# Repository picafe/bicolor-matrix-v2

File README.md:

# Bicolour Matrix

A 32x8 bicolor LED matrix module composed of 4 8x8 matrices based on the Holtek HT16K33A I2C LED driver. V1 paired it with a stacked adapter (RP2040 Zero + DS3231 module); V2 redesigns the matrix routing and puts an ESP32-C3, RTC, and environment sensors on a half-length adapter board behind the display.

*V1 running as a clock*

## Inspiration

Inspired by the common 32x8 red LED matrix modules that use the MAX7219 IC, I wanted to make my own module but with more colours and functionality, while keeping the same asthetic.

I found [these](https://www.aliexpress.com/item/1005007029570407.html) modules while browsing Aliexpress and thought they could look be a cool alternative, costing ~$15 for 10 modules. With the red and light green variant, you can have red, a light green, and orange all in one module. As far as I'm aware, there aren't RGB modules in a similar form factor, although you can take generic WS2818 8x8 matricies and 3D print a diffuser for them, although the footprint is much bigger. This project was also partially inspired by [bitluni's LED magnet tiles](https://www.youtube.com/watch?v=L2J_eNgjxio) which I found really cool.

Unlike the single colour matricies with 16 pins, these had 24. I found [this](https://www.adafruit.com/product/902) Adafruit module and followed a similar schematic with the Holtek HT16K33A I2C LED driver.

For V2 I revisited the HT16K33A datasheet and realized any ROW/COL pin can map to any matrix row/column, thus routing got a lot simpler than matching Adafruit's pinout exactly.

## Structure

| Board | Role |
| --- | --- |
| **bicolour-matrix** | 32×8 display: 4× HT16K33A + 4× 8×8 bicolour matrices |
| **adapter-board-r2** | ESP32-C3-WROOM-02, CH340X USB-UART, YSN8900 RTC + CR2032, STCC4 (default CO₂; optional SCD41), SHT4x, BMP580, LIS2DW12 |
| **button-board-r2** *(optional / WIP)* | OLED + light sensor + touch pads |

The adapter is half the length of the matrix board and mates with a pin header between the middle modules so that the stack stays stable without a case.

The button board is a separate interface that is connected to the adapter board with a 7-pin JST SH connector. This is meant to be customized and built by the user themselves, although I've included a sample design with an OLED, light sensor, and 2x touch pads you can start from. What you include and how you integrate it is up to you and how you want to design an enclosure.

## Pictures

### Assembled (V1)

### V2 

#### 3D

*Adapter board R2 (3D)*

*Matrix board R2 (3D)*

#### Schematics

*Matrix board schematic*

*Adapter board R2 schematic*

#### PCB

*Matrix board PCB (four HT16K33A modules)*

*Adapter board R2 PCB*

## Bill of materials

Prices are estimated from LCSC single-board quantities and AliExpress for the LED matrices.

### Matrix board (`bicolour-matrix`)

| Designator | Value | Footprint | Qty | LCSC | Unit cost (est.) | Line total (est.) |
| --- | --- | --- | --- | --- | --- | --- |
| C1, C6 | 10 µF | 0805 | 2 | C440198 | $0.02 | $0.04 |
| C2, C3, C4, C5 | 100 nF | 0603 | 4 | C14663 | $0.01 | $0.04 |
| D1, D2, D3, D4 | 1N4148WS | SOD-323 | 4 | C2128 | $0.01 | $0.04 |
| J1, J2 | 1×04 pin header | Through hole | 2 | — | $0.05 | $0.10 |
| J3, J4 | JST SH 1×04 (Qwiic-style) | SMD | 2 | — | $0.15 | $0.30 |
| J5 | 1×02 socket | Through hole | 1 | — | $0.05 | $0.05 |
| LED1, LED2, LED3, LED4 | 8×8 bicolour matrix | Module | 4 | AliExpress | $2.00 | $8.00 |
| R3, R4, R5, R9, R10, R11, R13, R14, R15, R18, R19, R20 | 47 kΩ | 0603 | 12 | C25819 | $0.002 | $0.02 |
| U1, U2, U3, U4 | HT16K33A | SSOP-28 | 4 | C5444738 | $0.54 | $2.16 |
| | | | | **Total (matrix, components only)** | | **~$10.75** |

### Adapter board (`adapter-board-r2`)

Default build uses the STCC4 for CO₂. An SCD41 (U7) can be fitted instead if R6/R8 are left open and the unpopulated R5/R7 0 Ω jumpers are fitted (routes the SHT4x onto the main I²C bus instead of the STCC4 compensation bus).

| Designator | Value | Footprint | Qty | LCSC | Unit cost (est.) | Line total (est.) |
| --- | --- | --- | --- | --- | --- | --- |
| BT1 | CR2032 holder | SMD | 1 | C7498149 | $0.15 | $0.15 |
| C1 | 1 µF | 0603 | 1 | C15849 | $0.01 | $0.01 |
| C3, C5, C11, C12, C18 | 100 nF | 0603 | 5 | C14663 | $0.01 | $0.05 |
| C4, C8, C9, C10, C13, C14, C16, C17 | 100 nF | 0402 | 8 | C1525 | $0.005 | $0.04 |
| C15 | 10 µF | 0603 | 1 | C19702 | $0.02 | $0.02 |
| C2 | 10 µF | 0805 | 1 | C15850 | $0.03 | $0.03 |
| C6, C7 | 4.7 µF | 1206 | 2 | C29823 | $0.03 | $0.06 |
| D1 | B5817WS | SOD-323 | 1 | C7420329 | $0.05 | $0.05 |
| F1, F2 | 1.1 A fuse | 0805 | 2 | — | $0.05 | $0.10 |
| J1 | USB-C receptacle 14P | Through hole | 1 | C3151746 | $0.30 | $0.30 |
| J2 | JST SH 1×07 | SMD | 1 | — | $0.25 | $0.25 |
| J3 | 1×02 socket | Through hole | 1 | — | $0.05 | $0.05 |
| J4 | 1×04 socket | Through hole | 1 | — | $0.08 | $0.08 |
| Q1 | UMH3N | SOT-363 | 1 | — | $0.08 | $0.08 |
| Q2, Q3 | BSS138W | SOT-323 | 2 | C28646265 | $0.03 | $0.06 |
| R1, R2 | 10 kΩ | 0603 | 2 | C25804 | $0.002 | $0.004 |
| R3, R4 | 5.1 kΩ | 0603 | 2 | C23186 | $0.002 | $0.004 |
| R6, R8 | 0 Ω (STCC4 / SHT4x compensation) | 0402 | 2 | C17168 | $0.004 | $0.008 |
| R9, R10, R11, R12 | 4.7 kΩ | 0603 | 4 | C23162 | $0.002 | $0.008 |
| S1, S2 | Tactile button, 160 gf | PTS810 | 2 | C720477 | $0.10 | $0.20 |
| U1 | ESP32-C3-WROOM-02 | Module | 1 | C2934560 | $3.13 | $3.13 |
| U2 | USBLC6-2SC6 | SOT-23-6 | 1 | C7519 | $0.18 | $0.18 |
| U3 | CH340X | MSOP-10 | 1 | C3035748 | $0.67 | $0.67 |
| U4 | AP2114HA-3.3TRG1 | SOT-223 | 1 | C460314 | $0.25 | $0.25 |
| U5 | YSN8900AP3 | SMD3225-10P | 1 | C54780223 | $1.46 | $1.46 |
| U6 | SHT4x | DFN-4 | 1 | — | $1.20 | $1.20 |
| U8 | BMP580 | LGA-10 | 1 | C22391138 | $0.96 | $0.96 |
| U9 | LIS2DW12TR | LGA-12 | 1 | C189624 | $1.26 | $1.26 |
| U10 | STCC4 | LGA | 1 | C49191471 | $10.06 | $10.06 |
| | | | | **Total (adapter, default build)** | | **~$20.73** |

Optional (not in default total): U7 SCD41 (~$18, C3659421) with R5/R7 fitted and R6/R8 open; leave U10 unpopulated.

**Combined components (matrix + adapter, default): ~$31.48**  
*(PCBs: ~$30 matrix + ~$12 adapter at JLCPCB)*

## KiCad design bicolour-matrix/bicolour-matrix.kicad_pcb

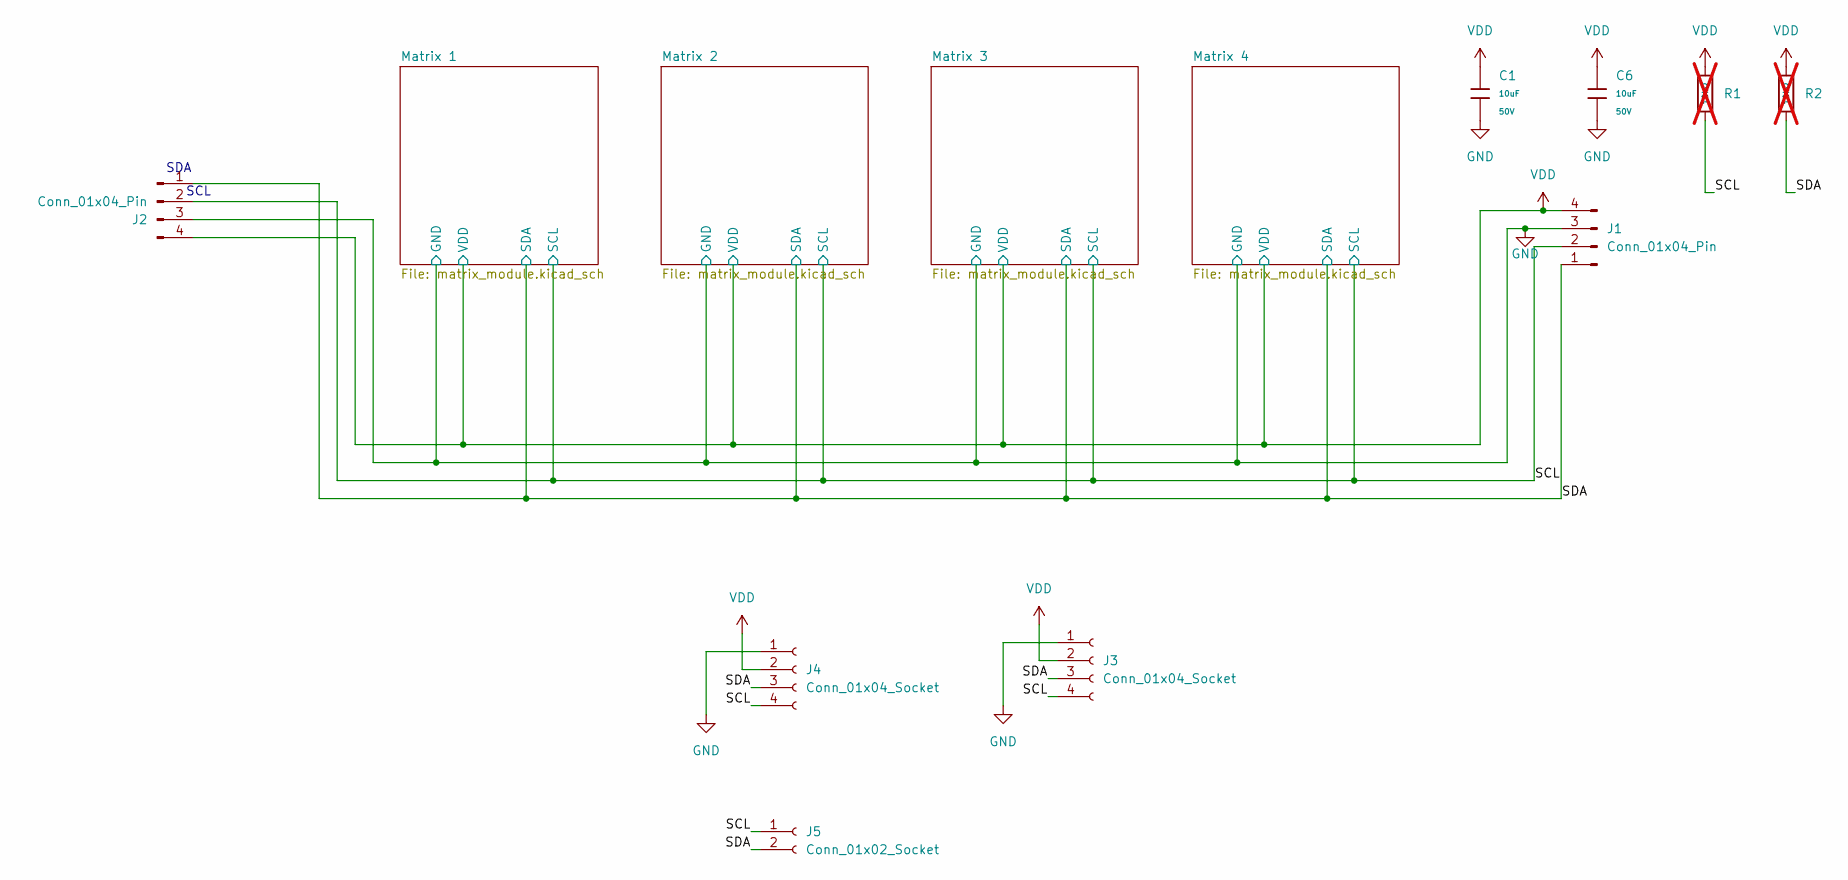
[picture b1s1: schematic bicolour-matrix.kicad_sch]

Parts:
C1, C6: 10uF; C_0805; Voltage Rated 50V; Tolerance ±10%; Part GRM21BR61H106KE43L; LCSC C440198
J1, J2: Conn_01x04_Pin; PinHeader_1x04_P2.54mm_Vertical
J3, J4: Conn_01x04_Socket; JST_SH_SM04B-SRSS-TB_1x04-1MP_P1.00mm_Horizontal
J5: Conn_01x02_Socket; PinSocket_1x02_P2.54mm_Vertical
R1, R2: 10kΩ; R_0603_1608Metric; Overload Voltage (Max) 75V; Tolerance ±1%; Part 0603WAF1002T5E; LCSC C25804; not fitted

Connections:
/SCL: J1.2, J2.2, J3.4, J4.4, J5.1, R1.2; also elsewhere on the board
/SDA: J1.1, J2.1, J3.3, J4.3, J5.2, R2.2; also elsewhere on the board
GND: C1.2, C6.2, J1.3, J2.3, J3.1, J4.1; also elsewhere on the board
VDD: C1.1, C6.1, J1.4, J2.4, J3.2, J4.2, R1.1, R2.1; also elsewhere on the board

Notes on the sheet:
SDA
SCL

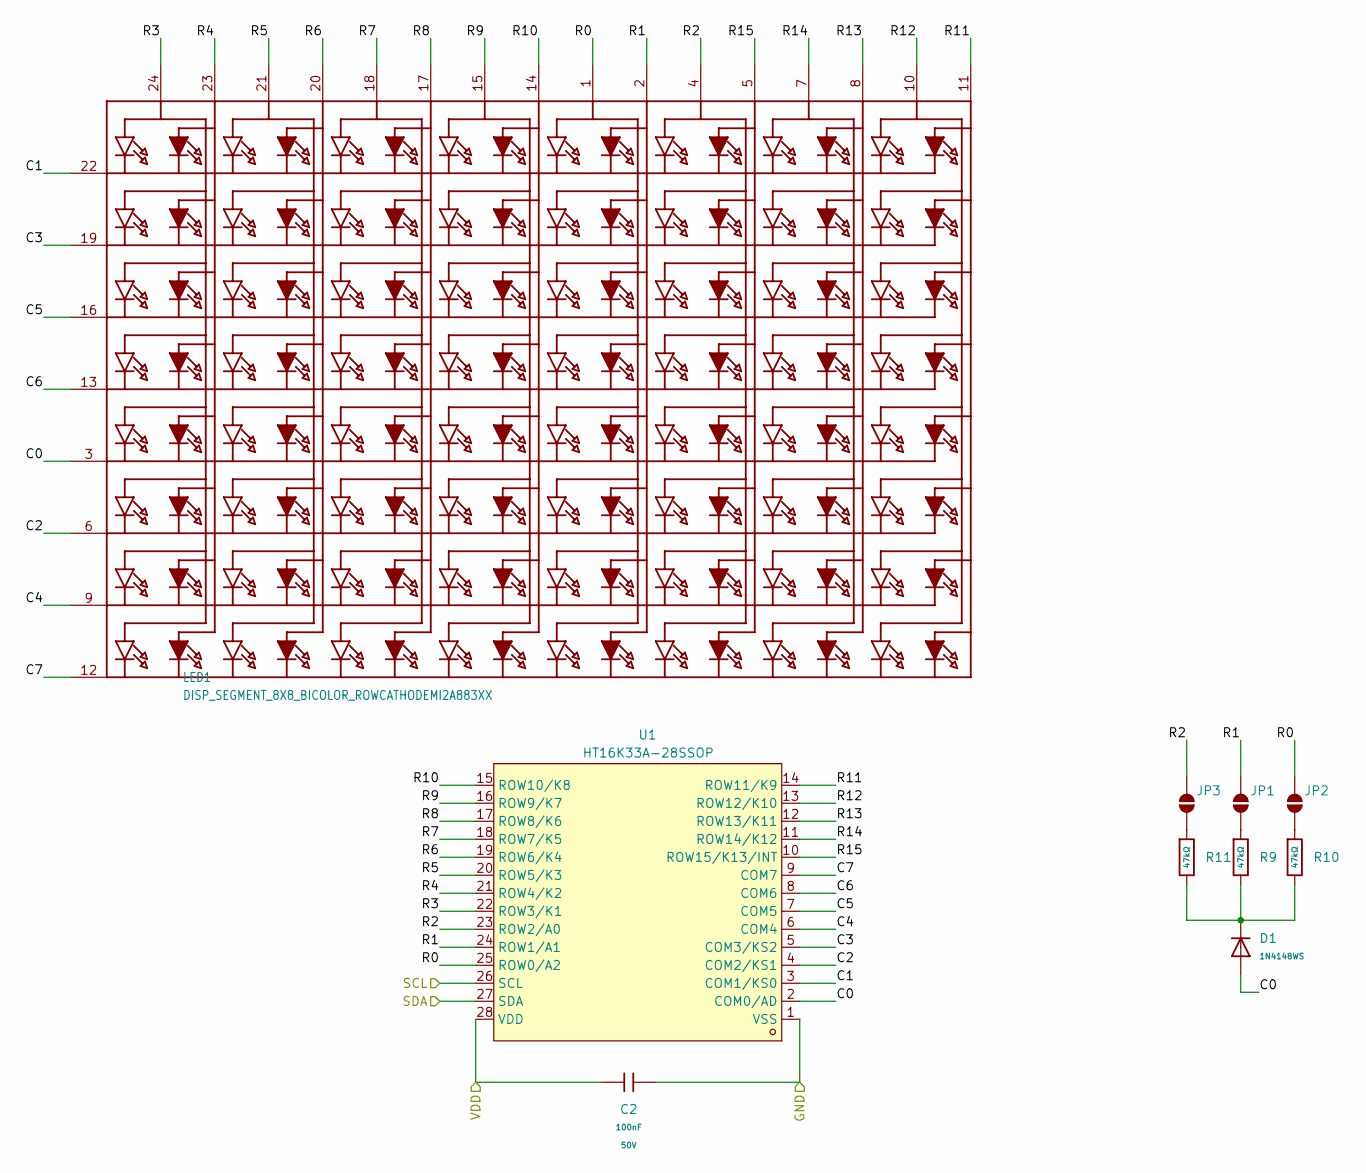
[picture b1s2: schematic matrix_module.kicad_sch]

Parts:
C2: 100nF; C_0603; Voltage Rated 50V; Tolerance ±10%; Part CC0603KRX7R9BB104; LCSC C14663
D1: 1N4148WS; D_SOD-323; Forward Voltage (Vf@If) 1.25V@150mA; Reverse Voltage (Vr) 100V; Part 1N4148WS; LCSC C2128
JP1, JP2, JP3: SolderJumper_2_Open; SolderJumper-2_P1.3mm_Open_RoundedPad1.0x1.5mm
LED1: DISP_SEGMENT_8X8_BICOLOR_ROWCATHODEMI2A883XX; SEGMENT_BICOL_BL-M12A883XX
R9, R10, R11: 47kΩ; R_0603; Overload Voltage (Max) 75V; Tolerance ±1%; Part 0603WAF4702T5E; LCSC C25819
U1: HT16K33A-28SSOP; SSOP-28_3.9x9.9mm_P0.635mm; LCSC Part C5444738

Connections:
/Matrix 1/C0: D1.2, LED1.3 (K5), U1.2 (COM0/AD)
/Matrix 1/C1: LED1.22 (K1), U1.3 (COM1/KS0)
/Matrix 1/C2: LED1.6 (K6), U1.4 (COM2/KS1)
/Matrix 1/C3: LED1.19 (K2), U1.5 (COM3/KS2)
/Matrix 1/C4: LED1.9 (K7), U1.6 (COM4)
/Matrix 1/C5: LED1.16 (K3), U1.7 (COM5)
/Matrix 1/C6: LED1.13 (K4), U1.8 (COM6)
/Matrix 1/C7: LED1.12 (K8), U1.9 (COM7)
/Matrix 1/R0: JP2.2 (B), LED1.1 (A9), U1.25 (ROW0/A2)
/Matrix 1/R1: JP1.2 (B), LED1.2 (A10), U1.24 (ROW1/A1)
/Matrix 1/R2: JP3.2 (B), LED1.4 (A11), U1.23 (ROW2/A0)
/Matrix 1/R3: LED1.24 (A1), U1.22 (ROW3/K1)
/Matrix 1/R4: LED1.23 (A2), U1.21 (ROW4/K2)
/Matrix 1/R5: LED1.21 (A3), U1.20 (ROW5/K3)
/Matrix 1/R6: LED1.20 (A4), U1.19 (ROW6/K4)
/Matrix 1/R7: LED1.18 (A5), U1.18 (ROW7/K5)
/Matrix 1/R8: LED1.17 (A6), U1.17 (ROW8/K6)
/Matrix 1/R9: LED1.15 (A7), U1.16 (ROW9/K7)
/Matrix 1/R10: LED1.14 (A8), U1.15 (ROW10/K8)
/Matrix 1/R11: LED1.11 (A16), U1.14 (ROW11/K9)
/Matrix 1/R12: LED1.10 (A15), U1.13 (ROW12/K10)
/Matrix 1/R13: LED1.8 (A14), U1.12 (ROW13/K11)
/Matrix 1/R14: LED1.7 (A13), U1.11 (ROW14/K12)
/Matrix 1/R15: LED1.5 (A12), U1.10 (ROW15/K13/INT)
/SCL: U1.26 (SCL); also elsewhere on the board
/SDA: U1.27 (SDA); also elsewhere on the board
GND: C2.2, U1.1 (VSS); also elsewhere on the board
unnamed: D1.1, R9.2, R10.2, R11.2
unnamed: JP1.1 (A), R9.1
unnamed: JP2.1 (A), R10.1
unnamed: JP3.1 (A), R11.1
VDD: C2.1, U1.28 (VDD); also elsewhere on the board

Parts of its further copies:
C3, C4, C5: 100nF; C_0603; Voltage Rated 50V; Tolerance ±10%; Part CC0603KRX7R9BB104; LCSC C14663
D2, D3, D4: 1N4148WS; D_SOD-323; Forward Voltage (Vf@If) 1.25V@150mA; Reverse Voltage (Vr) 100V; Part 1N4148WS; LCSC C2128
JP4, JP5, JP6, JP7, JP8, JP9, JP10, JP11, JP12: SolderJumper_2_Open; SolderJumper-2_P1.3mm_Open_RoundedPad1.0x1.5mm
LED2, LED3, LED4: DISP_SEGMENT_8X8_BICOLOR_ROWCATHODEMI2A883XX; SEGMENT_BICOL_BL-M12A883XX
R3, R4, R5, R13, R14, R15, R18, R19, R20: 47kΩ; R_0603; Overload Voltage (Max) 75V; Tolerance ±1%; Part 0603WAF4702T5E; LCSC C25819
U2, U3, U4: HT16K33A-28SSOP; SSOP-28_3.9x9.9mm_P0.635mm; LCSC Part C5444738

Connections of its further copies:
/Matrix 2/C0: D2.2, LED2.3 (K5), U2.2 (COM0/AD)
/Matrix 2/C1: LED2.22 (K1), U2.3 (COM1/KS0)
/Matrix 2/C2: LED2.6 (K6), U2.4 (COM2/KS1)
/Matrix 2/C3: LED2.19 (K2), U2.5 (COM3/KS2)
/Matrix 2/C4: LED2.9 (K7), U2.6 (COM4)
/Matrix 2/C5: LED2.16 (K3), U2.7 (COM5)
/Matrix 2/C6: LED2.13 (K4), U2.8 (COM6)
/Matrix 2/C7: LED2.12 (K8), U2.9 (COM7)
/Matrix 2/R0: JP6.2 (B), LED2.1 (A9), U2.25 (ROW0/A2)
/Matrix 2/R1: JP5.2 (B), LED2.2 (A10), U2.24 (ROW1/A1)
/Matrix 2/R2: JP4.2 (B), LED2.4 (A11), U2.23 (ROW2/A0)
/Matrix 2/R3: LED2.24 (A1), U2.22 (ROW3/K1)
/Matrix 2/R4: LED2.23 (A2), U2.21 (ROW4/K2)
/Matrix 2/R5: LED2.21 (A3), U2.20 (ROW5/K3)
/Matrix 2/R6: LED2.20 (A4), U2.19 (ROW6/K4)
/Matrix 2/R7: LED2.18 (A5), U2.18 (ROW7/K5)
/Matrix 2/R8: LED2.17 (A6), U2.17 (ROW8/K6)
/Matrix 2/R9: LED2.15 (A7), U2.16 (ROW9/K7)
/Matrix 2/R10: LED2.14 (A8), U2.15 (ROW10/K8)
/Matrix 2/R11: LED2.11 (A16), U2.14 (ROW11/K9)
/Matrix 2/R12: LED2.10 (A15), U2.13 (ROW12/K10)
/Matrix 2/R13: LED2.8 (A14), U2.12 (ROW13/K11)
/Matrix 2/R14: LED2.7 (A13), U2.11 (ROW14/K12)
/Matrix 2/R15: LED2.5 (A12), U2.10 (ROW15/K13/INT)
/Matrix 3/C0: D3.2, LED3.3 (K5), U3.2 (COM0/AD)
/Matrix 3/C1: LED3.22 (K1), U3.3 (COM1/KS0)
/Matrix 3/C2: LED3.6 (K6), U3.4 (COM2/KS1)
/Matrix 3/C3: LED3.19 (K2), U3.5 (COM3/KS2)
/Matrix 3/C4: LED3.9 (K7), U3.6 (COM4)
/Matrix 3/C5: LED3.16 (K3), U3.7 (COM5)
/Matrix 3/C6: LED3.13 (K4), U3.8 (COM6)
/Matrix 3/C7: LED3.12 (K8), U3.9 (COM7)
/Matrix 3/R0: JP9.2 (B), LED3.1 (A9), U3.25 (ROW0/A2)
/Matrix 3/R1: JP8.2 (B), LED3.2 (A10), U3.24 (ROW1/A1)
/Matrix 3/R2: JP7.2 (B), LED3.4 (A11), U3.23 (ROW2/A0)
/Matrix 3/R3: LED3.24 (A1), U3.22 (ROW3/K1)
/Matrix 3/R4: LED3.23 (A2), U3.21 (ROW4/K2)
/Matrix 3/R5: LED3.21 (A3), U3.20 (ROW5/K3)
/Matrix 3/R6: LED3.20 (A4), U3.19 (ROW6/K4)
/Matrix 3/R7: LED3.18 (A5), U3.18 (ROW7/K5)
/Matrix 3/R8: LED3.17 (A6), U3.17 (ROW8/K6)
/Matrix 3/R9: LED3.15 (A7), U3.16 (ROW9/K7)
/Matrix 3/R10: LED3.14 (A8), U3.15 (ROW10/K8)
/Matrix 3/R11: LED3.11 (A16), U3.14 (ROW11/K9)
/Matrix 3/R12: LED3.10 (A15), U3.13 (ROW12/K10)
/Matrix 3/R13: LED3.8 (A14), U3.12 (ROW13/K11)
/Matrix 3/R14: LED3.7 (A13), U3.11 (ROW14/K12)
/Matrix 3/R15: LED3.5 (A12), U3.10 (ROW15/K13/INT)
/Matrix 4/C0: D4.2, LED4.3 (K5), U4.2 (COM0/AD)
/Matrix 4/C1: LED4.22 (K1), U4.3 (COM1/KS0)
/Matrix 4/C2: LED4.6 (K6), U4.4 (COM2/KS1)
/Matrix 4/C3: LED4.19 (K2), U4.5 (COM3/KS2)
/Matrix 4/C4: LED4.9 (K7), U4.6 (COM4)
/Matrix 4/C5: LED4.16 (K3), U4.7 (COM5)
/Matrix 4/C6: LED4.13 (K4), U4.8 (COM6)
/Matrix 4/C7: LED4.12 (K8), U4.9 (COM7)
/Matrix 4/R0: JP12.2 (B), LED4.1 (A9), U4.25 (ROW0/A2)
/Matrix 4/R1: JP11.2 (B), LED4.2 (A10), U4.24 (ROW1/A1)
/Matrix 4/R2: JP10.2 (B), LED4.4 (A11), U4.23 (ROW2/A0)
/Matrix 4/R3: LED4.24 (A1), U4.22 (ROW3/K1)
/Matrix 4/R4: LED4.23 (A2), U4.21 (ROW4/K2)
/Matrix 4/R5: LED4.21 (A3), U4.20 (ROW5/K3)
/Matrix 4/R6: LED4.20 (A4), U4.19 (ROW6/K4)
/Matrix 4/R7: LED4.18 (A5), U4.18 (ROW7/K5)
/Matrix 4/R8: LED4.17 (A6), U4.17 (ROW8/K6)
/Matrix 4/R9: LED4.15 (A7), U4.16 (ROW9/K7)
/Matrix 4/R10: LED4.14 (A8), U4.15 (ROW10/K8)
/Matrix 4/R11: LED4.11 (A16), U4.14 (ROW11/K9)
/Matrix 4/R12: LED4.10 (A15), U4.13 (ROW12/K10)
/Matrix 4/R13: LED4.8 (A14), U4.12 (ROW13/K11)
/Matrix 4/R14: LED4.7 (A13), U4.11 (ROW14/K12)
/Matrix 4/R15: LED4.5 (A12), U4.10 (ROW15/K13/INT)
/SCL: U2.26 (SCL), U3.26 (SCL), U4.26 (SCL); also elsewhere on the board
/SDA: U2.27 (SDA), U3.27 (SDA), U4.27 (SDA); also elsewhere on the board
GND: C3.2, C4.2, C5.2, U2.1 (VSS), U3.1 (VSS), U4.1 (VSS); also elsewhere on the board
unnamed: D2.1, R3.2, R4.2, R5.2
unnamed: D3.1, R13.2, R14.2, R15.2
unnamed: D4.1, R18.2, R19.2, R20.2
unnamed: JP4.1 (A), R3.1
unnamed: JP5.1 (A), R4.1
unnamed: JP6.1 (A), R5.1
unnamed: JP7.1 (A), R13.1
unnamed: JP8.1 (A), R14.1
unnamed: JP9.1 (A), R15.1
unnamed: JP10.1 (A), R18.1
unnamed: JP11.1 (A), R19.1
unnamed: JP12.1 (A), R20.1
VDD: C3.1, C4.1, C5.1, U2.28 (VDD), U3.28 (VDD), U4.28 (VDD); also elsewhere on the board

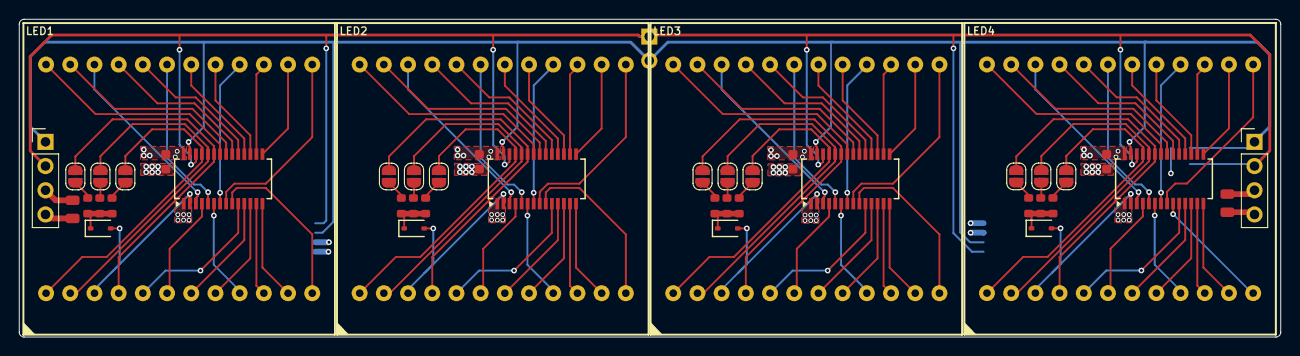
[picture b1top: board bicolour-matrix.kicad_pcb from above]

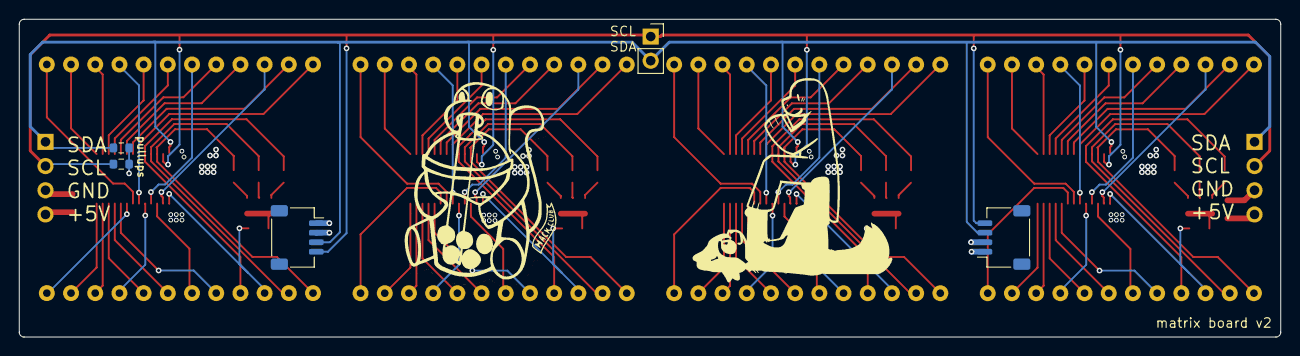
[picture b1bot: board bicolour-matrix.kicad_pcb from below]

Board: 4 copper layers, 132.4 x 33.4 mm, 49 parts (5 on the bottom side), 116 nets.

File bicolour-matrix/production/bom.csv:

Designator,Footprint,Quantity,Value,LCSC Part #
"C1, C6",C_0805,2,10uF,C440198
"C2, C3, C4, C5",C_0603,4,100nF,C14663
"D1, D2, D3, D4",D_SOD-323,4,1N4148WS,C2128
"J1, J2",PinHeader_1x04_P2.54mm_Vertical,2,Conn_01x04_Pin,
"J3, J4",JST_SH_SM04B-SRSS-TB_1x04-1MP_P1.00mm_Horizontal,2,Conn_01x04_Socket,
J5,PinSocket_1x02_P2.54mm_Vertical,1,Conn_01x02_Socket,
"LED1, LED2, LED3, LED4",SEGMENT_BICOL_BL-M12A883XX,4,DISP_SEGMENT_8X8_BICOLOR_ROWCATHODEMI2A883XX,
"R10, R11, R13, R14, R15, R18, R19, R20, R3, R4, R5, R9",R_0603,12,47kΩ,C25819
"U1, U2, U3, U4",SSOP-28_3.9x9.9mm_P0.635mm,4,HT16K33A-28SSOP,C5444738

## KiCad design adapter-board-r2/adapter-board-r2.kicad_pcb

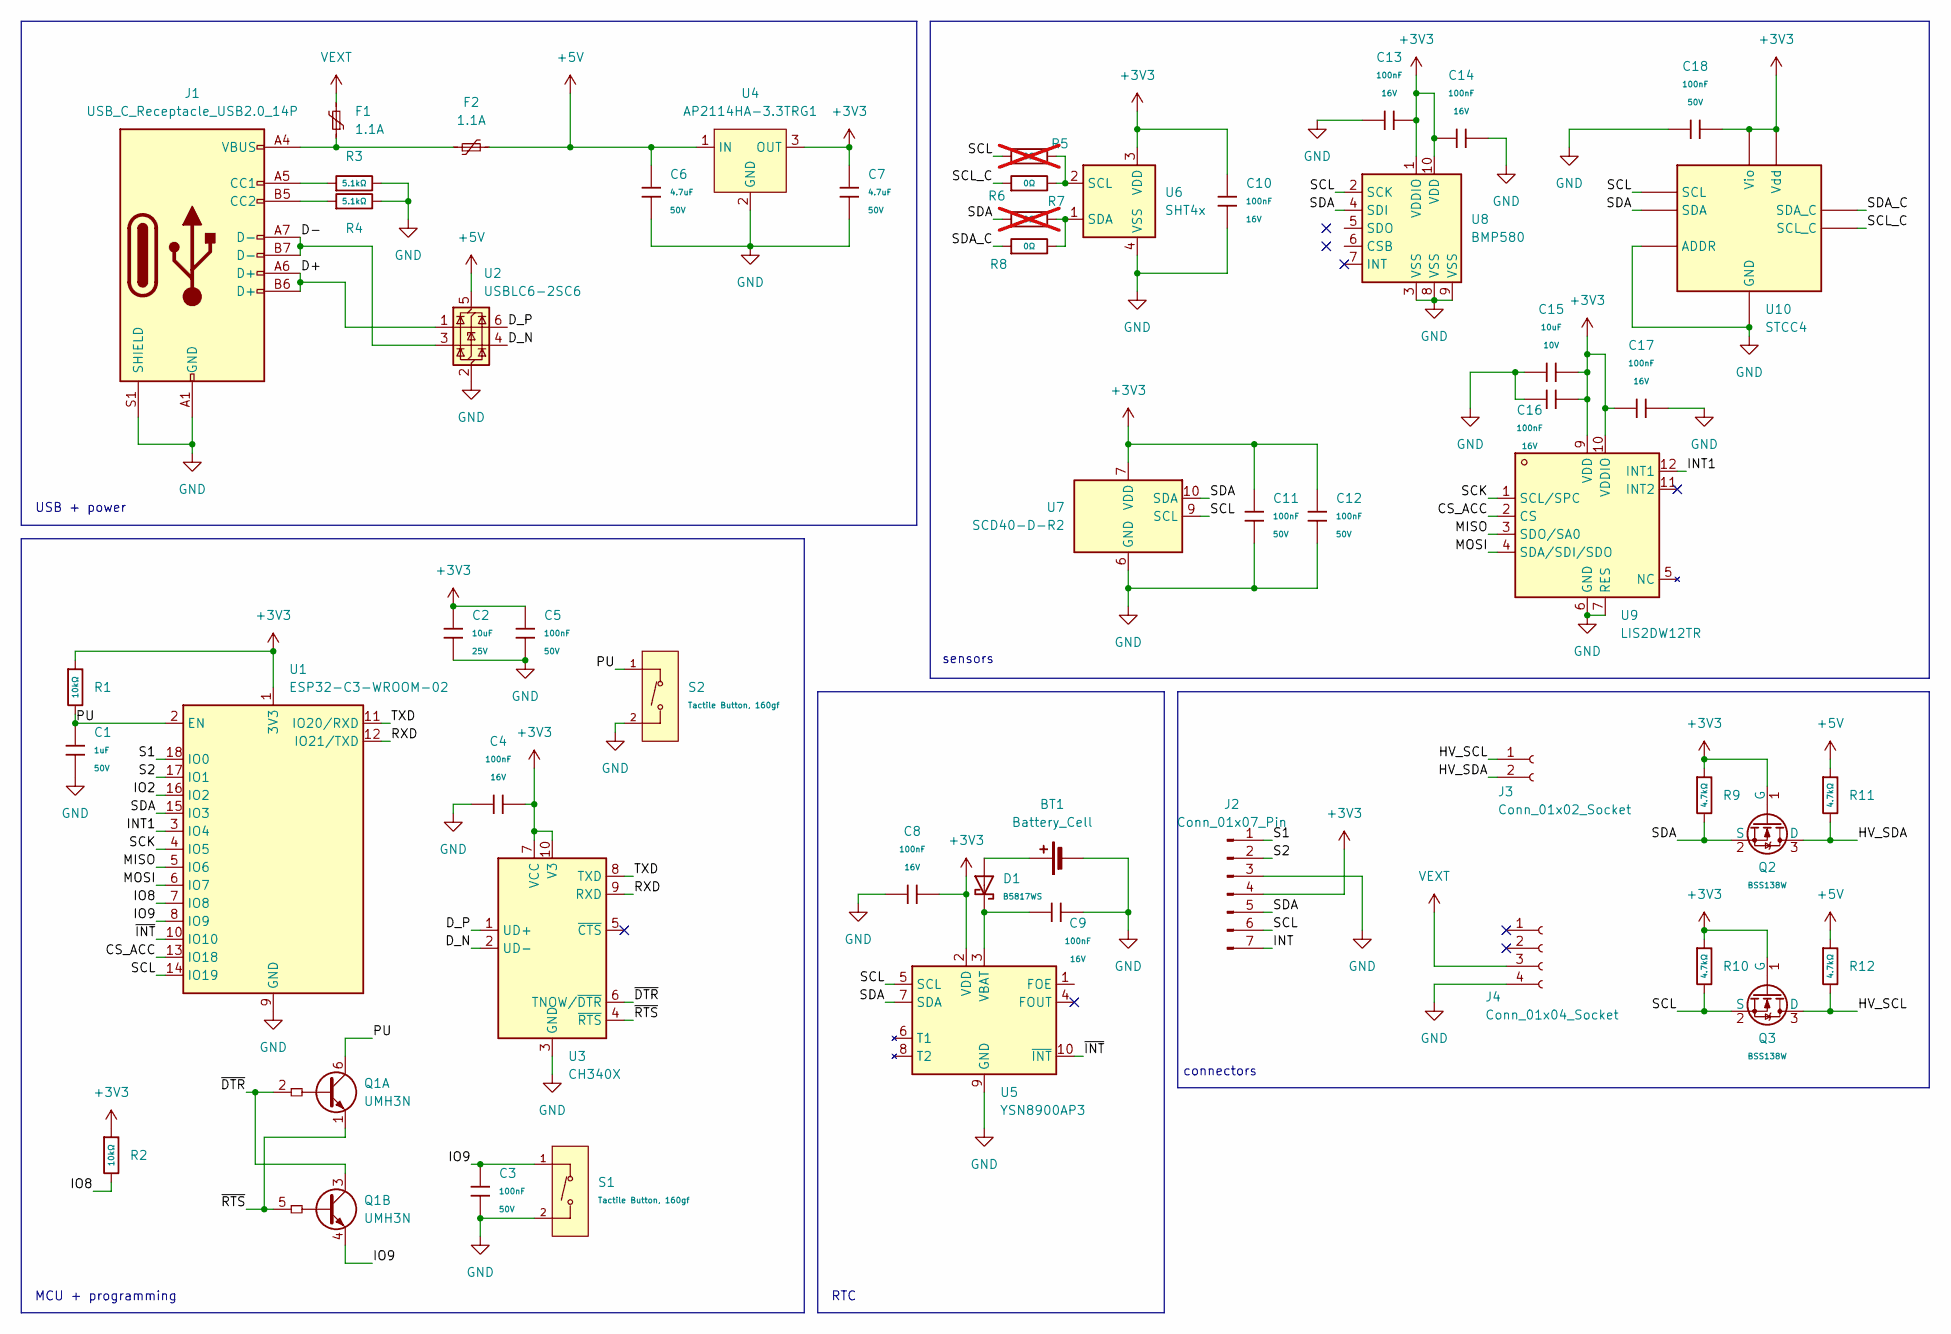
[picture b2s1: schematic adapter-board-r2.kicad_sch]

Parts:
BT1: Battery_Cell; BatteryHolder_Keystone_1060_1x2032
C1: 1uF; C_0603; Voltage Rated 50V; Tolerance ±10%; Part CL10A105KB8NNNC; LCSC C15849
C2: 10uF; C_0805; Voltage Rated 25V; Tolerance ±10%; Part CL21A106KAYNNNE; LCSC C15850
C3, C5, C11, C12, C18: 100nF; C_0603; Voltage Rated 50V; Tolerance ±10%; Part CC0603KRX7R9BB104; LCSC C14663
C4, C8, C9, C10, C13, C14, C16, C17: 100nF; C_0402; Voltage Rated 16V; Tolerance ±10%; Part CL05B104KO5NNNC; LCSC C1525
C6, C7: 4.7uF; C_1206; Voltage Rated 50V; Tolerance ±10%; Part 1206B475K500NT; LCSC C29823
C15: 10uF; C_0603; Voltage Rated 10V; Tolerance ±10%; Part CL10A106KP8NNNC; LCSC C19702
D1: B5817WS; D_SOD-323; Forward Voltage (Vf@If) 450mV@1.0A; Reverse Voltage (Vr) 20V; Part B5817WS; LCSC C7420329
F1, F2: 1.1A; Fuse_0805_2012Metric
J1: USB_C_Receptacle_USB2.0_14P; USB-C-TH_SHOUHAN_TYPE-C-14PLC-H10.0
J2: Conn_01x07_Pin; JST_SH_SM07B-SRSS-TB_1x07-1MP_P1.00mm_Horizontal
J3: Conn_01x02_Socket; PinSocket_1x02_P2.54mm_Vertical
J4: Conn_01x04_Socket; PinSocket_1x04_P2.54mm_Vertical
Q1: UMH3N; SOT-363_SC-70-6
Q2, Q3: BSS138W; SOT-323_SC-70; Part BSS138W; LCSC C28646265
R1, R2: 10kΩ; R_0603; Overload Voltage (Max) 75V; Tolerance ±1%; Part 0603WAF1002T5E; LCSC C25804
R3, R4: 5.1kΩ; R_0603; Overload Voltage (Max) 75V; Tolerance ±1%; Part 0603WAF5101T5E; LCSC C23186
R5, R7: 0Ω; R_0402; Overload Voltage (Max) 50V; Tolerance ±1%; Part 0402WGF0000TCE; LCSC C17168; not fitted
R6, R8: 0Ω; R_0402; Overload Voltage (Max) 50V; Tolerance ±1%; Part 0402WGF0000TCE; LCSC C17168
R9, R10, R11, R12: 4.7kΩ; R_0603; Overload Voltage (Max) 75V; Tolerance ±1%; Part 0603WAF4701T5E; LCSC C23162
S1, S2: Tactile Button, 160gf; SW_SPST_PTS810; Voltage Rating (Dc) 12V; Part TS-1088-AR02016; LCSC C720477
U1: ESP32-C3-WROOM-02
U2: USBLC6-2SC6; SOT-23-6
U3: CH340X; MSOP-10_3x3mm_P0.5mm
U4: AP2114HA-3.3TRG1; SOT-223; LCSC Part C460314
U5: YSN8900AP3; OSC-SMD_10P-L3.2-W2.5-BL_RX8130CE; MPN YSN8900AP3; LCSC Part C54780223
U6: SHT4x; Sensirion_DFN-4_1.5x1.5mm_P0.8mm_SHT4x_NoCentralPad
U7: SCD40-D-R2; Sensirion_SCD4x-1EP_10.1x10.1mm_P1.25mm_EP4.8x4.8mm
U8: BMP580; LGA-10_L2.0-W2.0-P0.50-TL_BMP580; MPN BMP580; LCSC Part C22391138
U9: LIS2DW12TR; LGA-12_2x2mm_P0.5mm; MPN LIS2DW12TR; LCSC Part C189624
U10: STCC4; LCSC C49191471

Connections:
+3V3: C2.1, C4.2, C5.1, C7.1, C8.2, C10.1, C11.1, C12.1, C13.2, C14.1, C15.2, C16.2, C17.1, C18.2, J2.4, Q2.1 (G), Q3.1 (G), R1.1, R2.1, R9.1, R10.1, U1.1 (3V3), U3.7 (VCC), U3.10 (V3), U4.3 (OUT), U5.2 (VDD), U6.3 (VDD), U7.7 (VDD), U7.19 (VDD), U8.1 (VDDIO), U8.10 (VDD), U9.9 (VDD), U9.10 (VDDIO), U10.6 (Vio), U10.7 (Vdd)
+5V: C6.1, F2.2, R11.1, R12.1, U2.5 (VBUS), U4.1 (IN)
/CS_ACC: U1.13 (IO18), U9.2 (CS)
/D+: J1.A6 (D+), J1.B6 (D+), U2.1 (I/O1)
/D-: J1.A7 (D-), J1.B7 (D-), U2.3 (I/O2)
/D_N: U2.4 (I/O2), U3.2 (UD-)
/D_P: U2.6 (I/O1), U3.1 (UD+)
/HV_SCL: J3.1, Q3.3 (D), R12.2
/HV_SDA: J3.2, Q2.3 (D), R11.2
/INT: J2.7
/INT1: U1.3 (IO4), U9.12 (INT1)
/IO2: U1.16 (IO2)
/IO8: R2.2, U1.7 (IO8)
/IO9: C3.1, Q1.4 (E2), S1.1 (A), U1.8 (IO9)
/MISO: U1.5 (IO6), U9.3 (SDO/SA0)
/MOSI: U1.6 (IO7), U9.4 (SDA/SDI/SDO)
/PU: C1.1, Q1.6 (C1), R1.2, S2.1 (A), U1.2 (EN)
/RXD: U1.12 (IO21/TXD), U3.9 (RXD)
/S1: J2.1, U1.18 (IO0)
/S2: J2.2, U1.17 (IO1)
/SCK: U1.4 (IO5), U9.1 (SCL/SPC)
/SCL: J2.6, Q3.2 (S), R5.1, R10.2, U1.14 (IO19), U5.5 (SCL), U7.9 (SCL), U8.2 (SCK), U10.1 (SCL)
/SCL_C: R6.1, U10.8 (SCL_C)
/SDA: J2.5, Q2.2 (S), R7.1, R9.2, U1.15 (IO3), U5.7 (SDA), U7.10 (SDA), U8.4 (SDI), U10.5 (SDA)
/SDA_C: R8.1, U10.2 (SDA_C)
/TXD: U1.11 (IO20/RXD), U3.8 (TXD)
/~DTR: Q1.2 (B1), Q1.3 (C2), U3.6 (TNOW/~DTR)
/~INT: U1.10 (IO10), U5.10 (~INT)
/~RTS: Q1.1 (E1), Q1.5 (B2), U3.4 (~RTS)
GND: BT1.2 (-), C1.2, C2.2, C3.2, C4.1, C5.2, C6.2, C7.2, C8.1, C9.2, C10.2, C11.2, C12.2, C13.1, C14.2, C15.1, C16.1, C17.2, C18.1, J1.A1 (GND), J1.A12 (GND), J1.B1 (GND), J1.B12 (GND), J1.S1 (SHIELD), J2.3, J4.4, R3.2, R4.2, S1.2 (B), S2.2 (B), U1.9 (GND), U1.19 (GND), U2.2 (GND), U3.3 (GND), U4.2 (GND), U4.4 (GND), U5.9 (GND), U6.4 (VSS), U7.6 (GND), U7.20 (GND), U7.21 (GND), U8.3 (VSS), U8.8 (VSS), U8.9 (VSS), U9.6 (GND), U9.7 (RES), U9.8 (GND), U10.3 (ADDR), U10.4 (GND)
unnamed: BT1.1 (+), D1.2
unnamed: F1.1, F2.1, J1.A4 (VBUS), J1.A9 (VBUS), J1.B4 (VBUS), J1.B9 (VBUS)
unnamed: J1.A5 (CC1), R3.1
unnamed: J1.B5 (CC2), R4.1
unnamed: C9.1, D1.1, U5.3 (VBAT)
unnamed: R5.2, R6.2, U6.2 (SCL)
unnamed: R7.2, R8.2, U6.1 (SDA)
VEXT: F1.2, J4.3

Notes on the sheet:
sensors
MCU + programming
RTC
connectors
USB + power

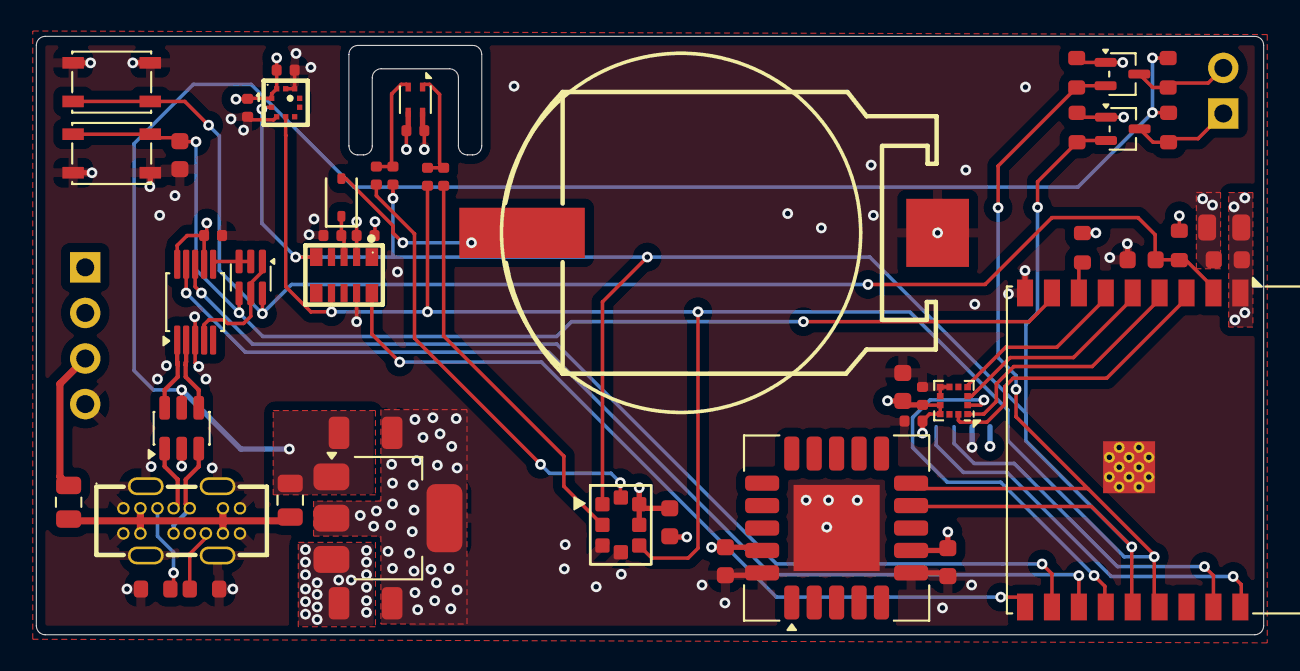
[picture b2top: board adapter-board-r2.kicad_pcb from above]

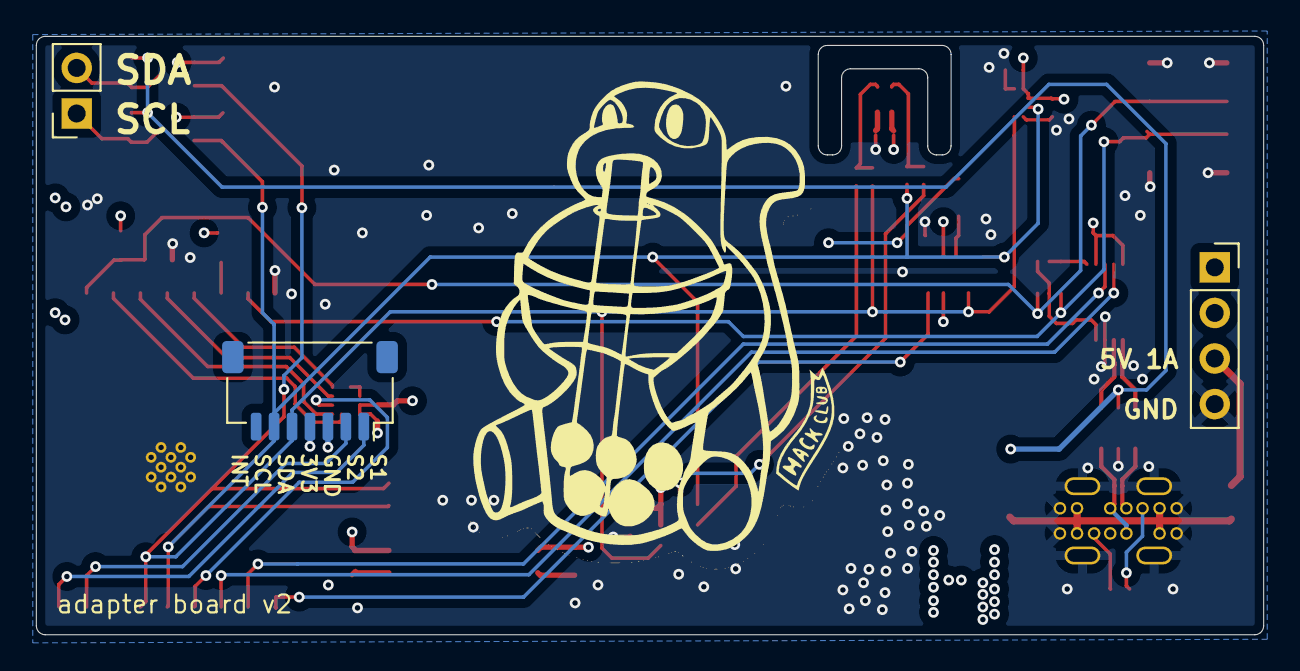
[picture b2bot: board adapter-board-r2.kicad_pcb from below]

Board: 4 copper layers, 68.4 x 33.3 mm, 53 parts (3 on the bottom side), 36 nets.

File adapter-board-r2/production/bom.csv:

Designator,Footprint,Quantity,Value,LCSC Part #
BT1,BAT-SMD_BS-CR2032-8,1,Battery_Cell,C7498149
C1,C_0603,1,1uF,C15849
"C10, C13, C14, C16, C17, C4, C8, C9",C_0402,8,100nF,C1525
"C11, C12, C18, C3, C5",C_0603,5,100nF,C14663
C15,C_0603,1,10uF,C19702
C2,C_0805,1,10uF,C15850
"C6, C7",C_1206,2,4.7uF,C29823
D1,D_SOD-323,1,B5817WS,C7420329
"F1, F2",0805,2,1.1A,
J1,USB-C-TH_SHOUHAN_TYPE-C-14PLC-H10.0,1,USB_C_Receptacle_USB2.0_14P,C3151746
J2,JST_SH_SM07B-SRSS-TB_1x07-1MP_P1.00mm_Horizontal,1,Conn_01x07_Pin,
J3,PinSocket_1x02_P2.54mm_Vertical,1,Conn_01x02_Socket,
J4,PinSocket_1x04_P2.54mm_Vertical,1,Conn_01x04_Socket,
Q1,SOT-363_SC-70-6,1,UMH3N,
"Q2, Q3",SOT-323_SC-70,2,BSS138W,C28646265
"R1, R2",R_0603,2,10kΩ,C25804
"R10, R11, R12, R9",R_0603,4,4.7kΩ,C23162
"R3, R4",R_0603,2,5.1kΩ,C23186
"R6, R8",R_0402,2,0Ω,C17168
"S1, S2",SW_SPST_PTS810,2,"Tactile Button, 160gf",C720477
U1,ESP32-C3-WROOM-02,1,ESP32-C3-WROOM-02,
U10,STCC4,1,STCC4,C49191471
U2,SOT-23-6,1,USBLC6-2SC6,
U3,MSOP-10_3x3mm_P0.5mm,1,CH340X,
U4,SOT-223,1,AP2114HA-3.3TRG1,C460314
U5,OSC-SMD_10P-L3.2-W2.5-BL_RX8130CE,1,YSN8900AP3,C54780223
U6,Sensirion_DFN-4_1.5x1.5mm_P0.8mm_SHT4x_NoCentralPad,1,SHT4x,
U7,Sensirion_SCD4x-1EP_10.1x10.1mm_P1.25mm_EP4.8x4.8mm,1,SCD40-D-R2,
U8,LGA-10_L2.0-W2.0-P0.50-TL_BMP580,1,BMP580,C22391138
U9,LGA-12_2x2mm_P0.5mm,1,LIS2DW12TR,C189624

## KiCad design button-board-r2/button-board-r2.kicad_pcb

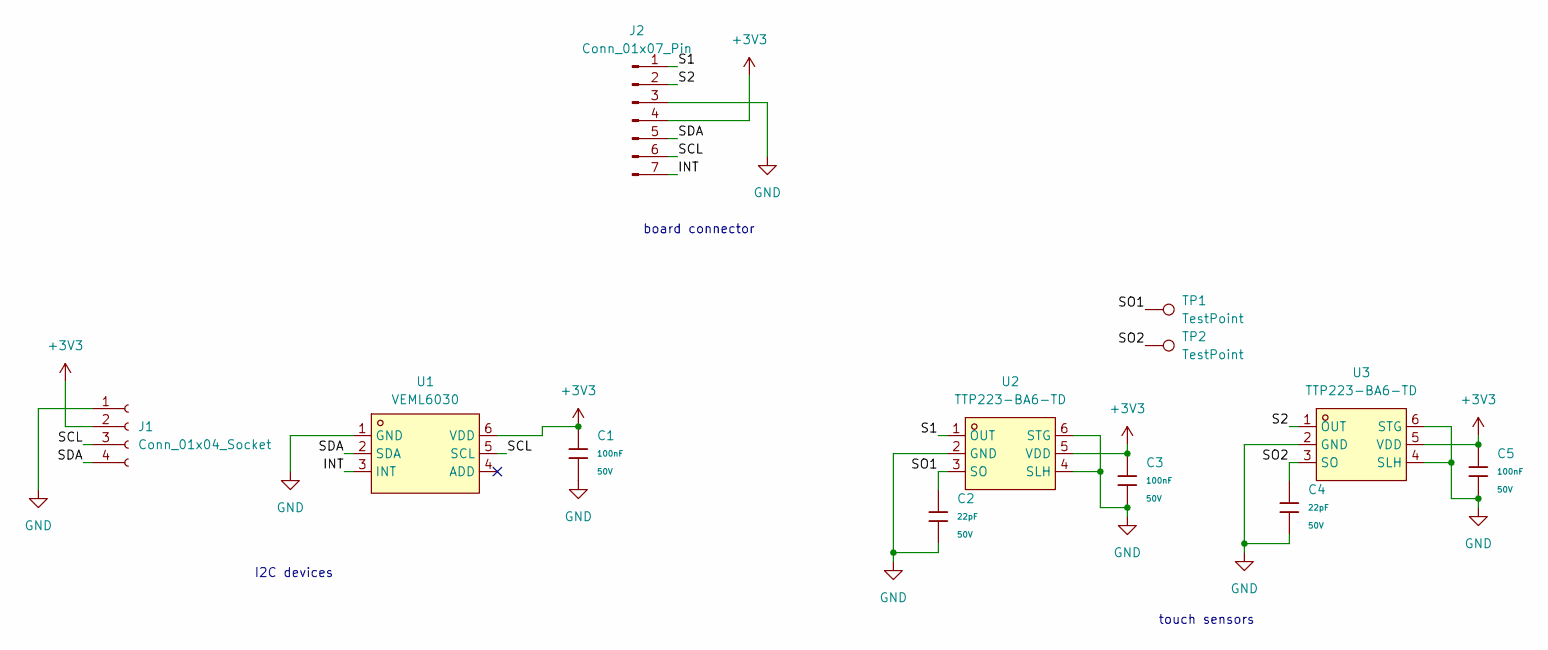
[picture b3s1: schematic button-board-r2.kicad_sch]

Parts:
C1, C3, C5: 100nF; C_0603; Voltage Rated 50V; Tolerance ±10%; Part CC0603KRX7R9BB104; LCSC C14663
C2, C4: 22pF; C_0603; Voltage Rated 50V; Tolerance ±5%; Part CL10C220JB8NNNC; LCSC C1653
J1: Conn_01x04_Socket; SSD1306-0.91-OLED-4pin-128x32
J2: Conn_01x07_Pin; JST_SH_SM07B-SRSS-TB_1x07-1MP_P1.00mm_Horizontal
TP1, TP2: TestPoint; TestPoint_Pad_D4.0mm
U1: VEML6030; SENSORS-SMD_VEML6030; MPN VEML6030; LCSC Part C132182
U2, U3: TTP223-BA6-TD; SOT-23-6_L2.9-W1.6-P0.95-LS2.9-BL; LCSC Part C42422127

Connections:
+3V3: C1.1, C3.1, C5.1, J1.2, J2.4, U1.6 (VDD), U2.5 (VDD), U3.5 (VDD)
/INT: J2.7, U1.3 (INT)
/S1: J2.1, U2.1 (OUT)
/S2: J2.2, U3.1 (OUT)
/SCL: J1.3, J2.6, U1.5 (SCL)
/SDA: J1.4, J2.5, U1.2 (SDA)
/SO1: C2.1, TP1.1, U2.3 (SO)
/SO2: C4.1, TP2.1, U3.3 (SO)
GND: C1.2, C2.2, C3.2, C4.2, C5.2, J1.1, J2.3, U1.1 (GND), U2.2 (GND), U2.4 (SLH), U2.6 (STG), U3.2 (GND), U3.4 (SLH), U3.6 (STG)

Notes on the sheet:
touch sensors
I2C devices
board connector

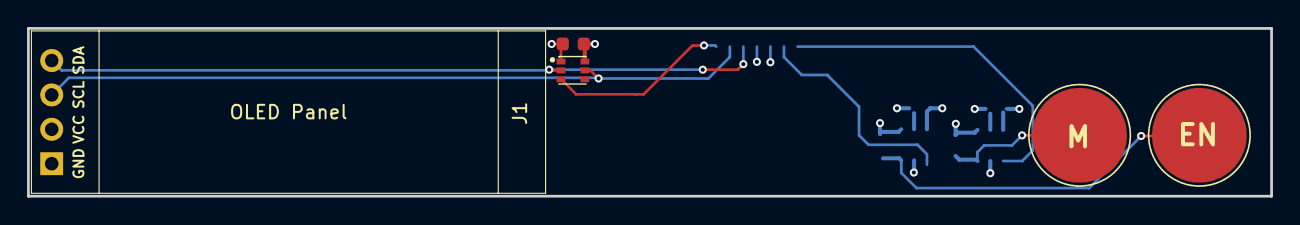
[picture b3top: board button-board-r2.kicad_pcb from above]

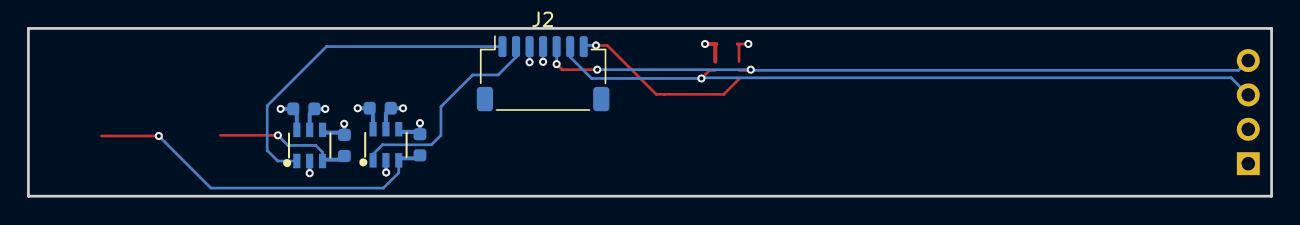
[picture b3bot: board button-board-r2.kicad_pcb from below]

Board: 4 copper layers, 91.9 x 12.4 mm, 12 parts (7 on the bottom side), 9 nets.
